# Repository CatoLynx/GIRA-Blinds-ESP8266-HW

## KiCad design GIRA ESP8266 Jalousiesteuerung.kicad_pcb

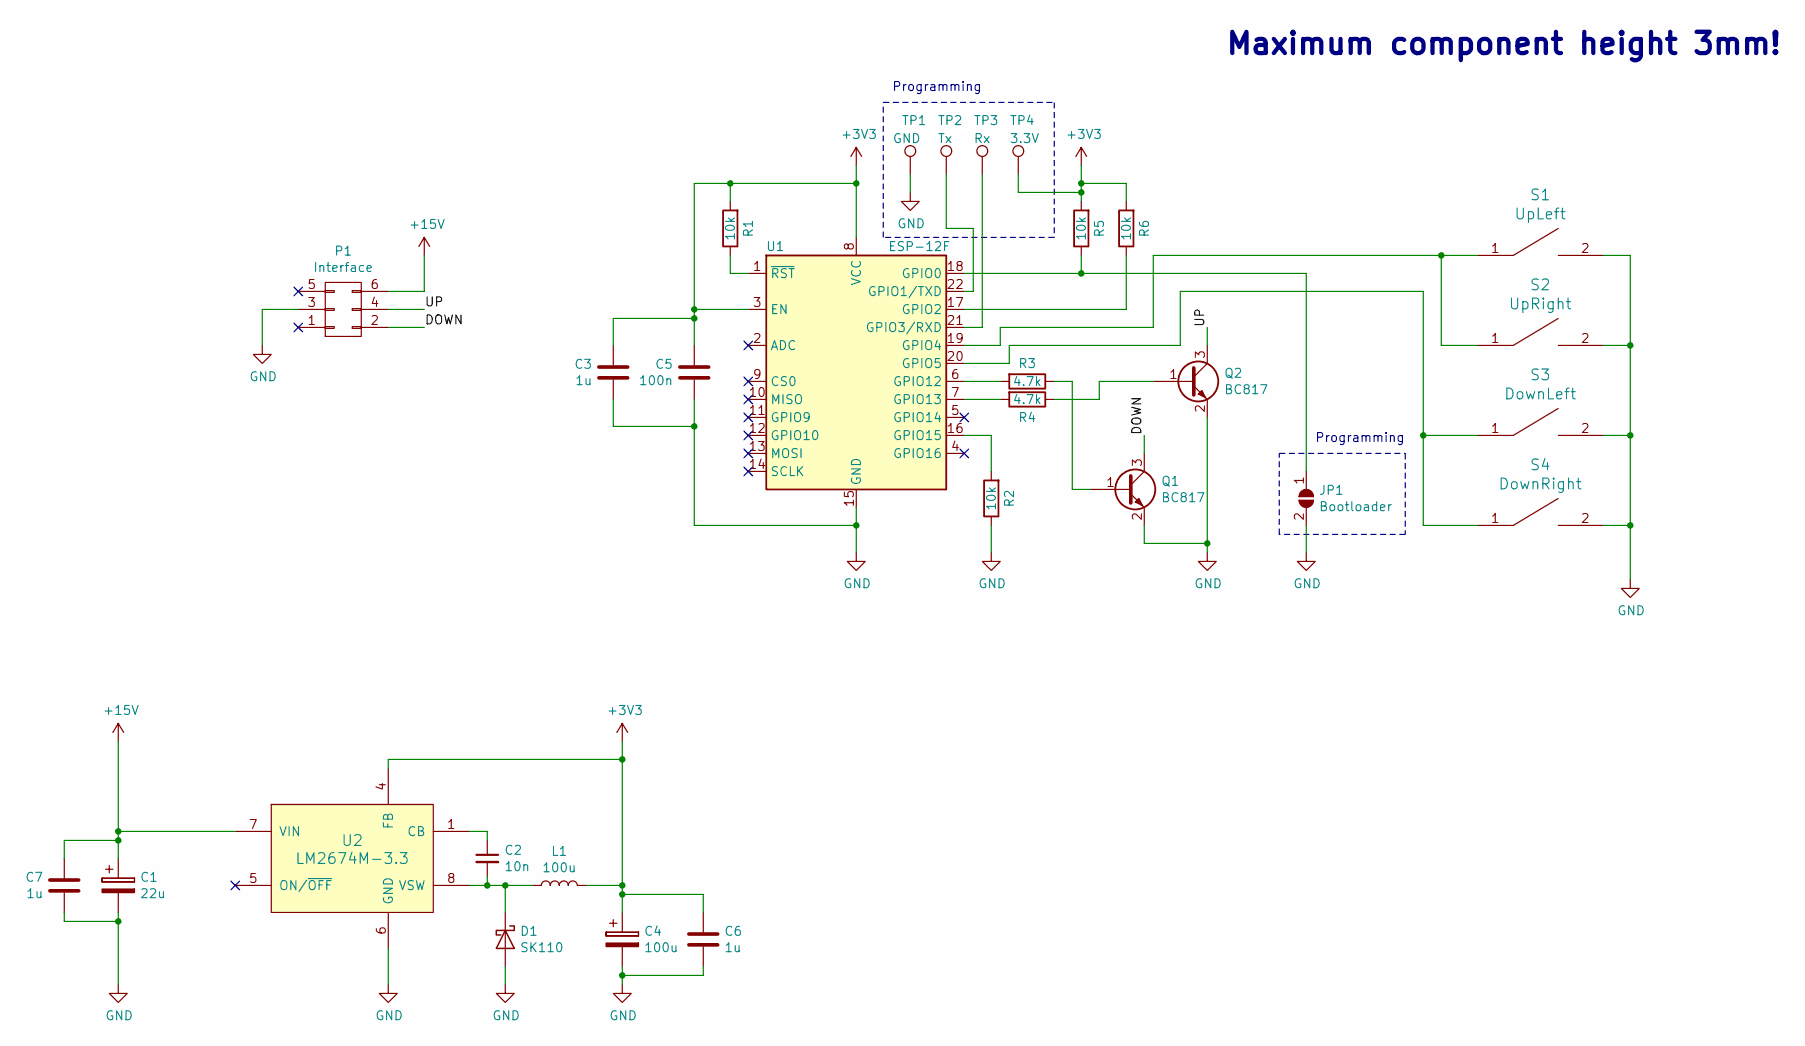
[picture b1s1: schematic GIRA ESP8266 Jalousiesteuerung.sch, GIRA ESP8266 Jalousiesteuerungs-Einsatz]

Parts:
C1: 22u; CP_Tantalum_Case-D_EIA-7343-31_Reflow
C2: 10n; C_0603
C3, C6, C7: 1u; C_0805
C4: 100u; CP_Tantalum_Case-D_EIA-7343-31_Reflow
C5: 100n; C_0603
D1: SK110; D_SMA_Standard
JP1: Bootloader; Jumper_SolderBridge
L1: 100u; L_1812
P1: Interface; Pin_Header_Straight_SMT_02x03
Q1, Q2: BC817; SOT-23
R1, R2, R5, R6: 10k; R_0603
R3, R4: 4.7k; R_0603
S1: UpLeft; Membrane_Switch_PCB_Only
S2: UpRight; Membrane_Switch_PCB_Only
S3: DownLeft; Membrane_Switch_PCB_Only
S4: DownRight; Membrane_Switch_PCB_Only
TP1: GND; Measurement_Point_Round-SMD-Pad_Small
TP2: Tx; Measurement_Point_Round-SMD-Pad_Small
TP3: Rx; Measurement_Point_Round-SMD-Pad_Small
TP4: 3.3V; Measurement_Point_Round-SMD-Pad_Small
U1: ESP-12F; ESP-12F_SMD
U2: LM2674M-3.3; SOIC-8_3.9x4.9mm_Pitch1.27mm

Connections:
+3V3: C3.2, C4.1, C5.2, C6.2, L1.2, R1.2, R5.2, R6.2, TP4.1, U1.3 (EN), U1.8 (VCC), U2.4 (FB)
+15V: C1.1, C7.2, P1.6, U2.7 (VIN)
/DOWN: P1.2, Q1.3 (C)
/UP: P1.4, Q2.3 (C)
GND: C1.2, C3.1, C4.2, C5.1, C6.1, C7.1, D1.2 (A), JP1.2 (B), P1.3, Q1.2 (E), Q2.2 (E), R2.1, S1.2, S2.2, S3.2, S4.2, TP1.1, U1.15 (GND), U2.6 (GND)
unnamed: C2.1, U2.1 (CB)
unnamed: C2.2, D1.1 (K), L1.1, U2.8 (VSW)
unnamed: JP1.1 (A), R5.1, U1.18 (GPIO0)
unnamed: Q1.1 (B), R3.1
unnamed: Q2.1 (B), R4.1
unnamed: R1.1, U1.1 (~RST)
unnamed: R2.2, U1.16 (GPIO15)
unnamed: R3.2, U1.6 (GPIO12)
unnamed: R4.2, U1.7 (GPIO13)
unnamed: R6.1, U1.17 (GPIO2)
unnamed: S1.1, S2.1, U1.19 (GPIO4)
unnamed: S3.1, S4.1, U1.20 (GPIO5)
unnamed: TP2.1, U1.22 (GPIO1/TXD)
unnamed: TP3.1, U1.21 (GPIO3/RXD)

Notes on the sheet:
Maximum component height 3mm!
Programming

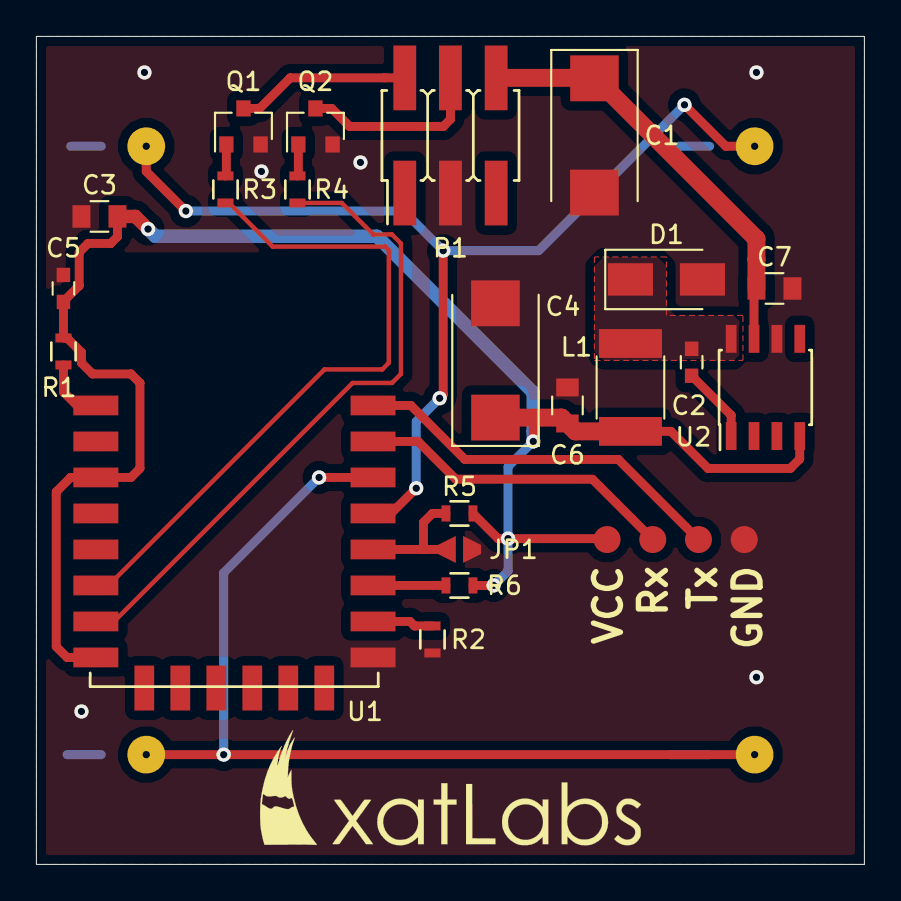
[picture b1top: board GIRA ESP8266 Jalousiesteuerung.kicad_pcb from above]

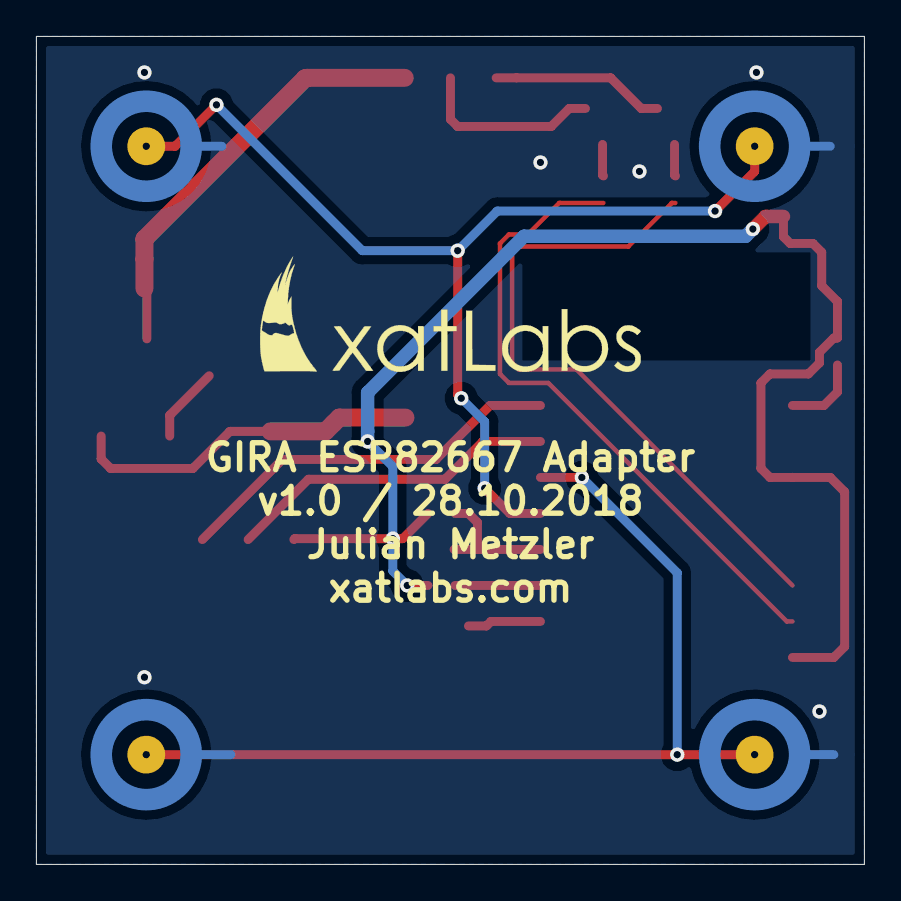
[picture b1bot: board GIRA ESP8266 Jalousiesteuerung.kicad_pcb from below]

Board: 2 copper layers, 46.0 x 46.0 mm, 29 parts (4 on the bottom side), 19 nets.

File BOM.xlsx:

Item | Reference(s) | Order No. | Value | Supplier | Qty
1 | C1 | 593D226X9035D2TE3 | 22u | TME | 1
2 | C2 | VJ0603Y103KXAPW1BC | 10n | TME | 1
3 | C3,C7,C6 | CL21B105KOFNNNG | 1u | TME | 3
4 | C4 | 293D107X9010D2TE3 | 100u | TME | 1
5 | C5 | VJ0603Y104KXACW1BC | 100n | TME | 1
6 | D1 | SK110-DIO | SK110 | TME | 1
8 | L1 | B82432T1104K | 100u | TME | 1
9 | P1 |  | Interface | TME | 1
10 | Q1,Q2 | BC817-16-DIO | BC817 | TME | 2
11 | R5,R6,R1,R2 | RC0603FR-0710K | 10k | TME | 4
12 | R4,R3 | RC0603FR-074K7 | 4.7k | TME | 2
17 | U1 |  | ESP-12F | eBay | 1
18 | U2 | LM2674M-3.3/NOP | LM2674M-3.3 | TME | 1

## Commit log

2018-10-30 First version
2018-10-31 Added BOM
2020-09-29 Update BOM, add TODO
